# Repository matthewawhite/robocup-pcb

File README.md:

View this project on [CADLAB.io](https://cadlab.io/project/2105). 

RoboCup PCB Repository
===========
Welcome to the Georgia Tech RoboJackets repository for management and storage of RoboCup's hardware files! Additional information about the team and current projects can be found on the [RoboJackets Website](http://www.robojackets.org/teams/robocup/) and the [RoboJacket Wiki](http://wiki.robojackets.org/w/RoboCup).

If you are a new member to the RoboCup electrical team and have never used *[git version control](http://git-scm.com/)* before, we highly recommend that you familiarize yourself with it.

## Prerequisites
- A computer configured with git [[Windows](https://windows.github.com)] [[Mac](https://mac.github.com/)]
- An installation of [EAGLE](http://www.cadsoftusa.com/)

## Using this Repository
Most CAD files found here are [EAGLE](http://www.cadsoftusa.com/) files. However, some older archived files were created using [PCB](http://pcb.geda-project.org) (a program that is part of the [gEDA project](http://www.geda-project.org)). Users will find the following items here:
- Control, Kicker, Antenna, and Base Station files
- Gerber files for most PCB designs
- RoboCup libraries
- DRU rulesets (for checking for errors)
- CAM Jobs (for exporting gerber files)

### Setup libraries in EAGLE

1. Downloading the libraries

	Once your computer is setup with git, the following lines can be used on any operating system within a *[terminal](http://en.wikipedia.org/wiki/Computer_terminal)* configured with git. Users who are using a GUI interface for git should simply add the respective repositories through the interface.

	```shell
    # Download the initial files
	$ git clone https://github.com/robojackets/robocup-pcb

    # Go into our new directory
    cd robocup-pcb

    # Download additional 3rd party libraries
    git submodule update --init
	```
2. Add the new directory locations to EAGLE:

	From EAGLE's Control Panel, navigate to the *Directories* window: *Options -> Directories*.

    Find the *Libraries* text box, and add the directory paths where the repositories were cloned from step 1. Don't forget to also include the path for the *[RoboJackets libraries](https://github.com/RoboJackets/robocup-pcb/tree/master/lib)*!

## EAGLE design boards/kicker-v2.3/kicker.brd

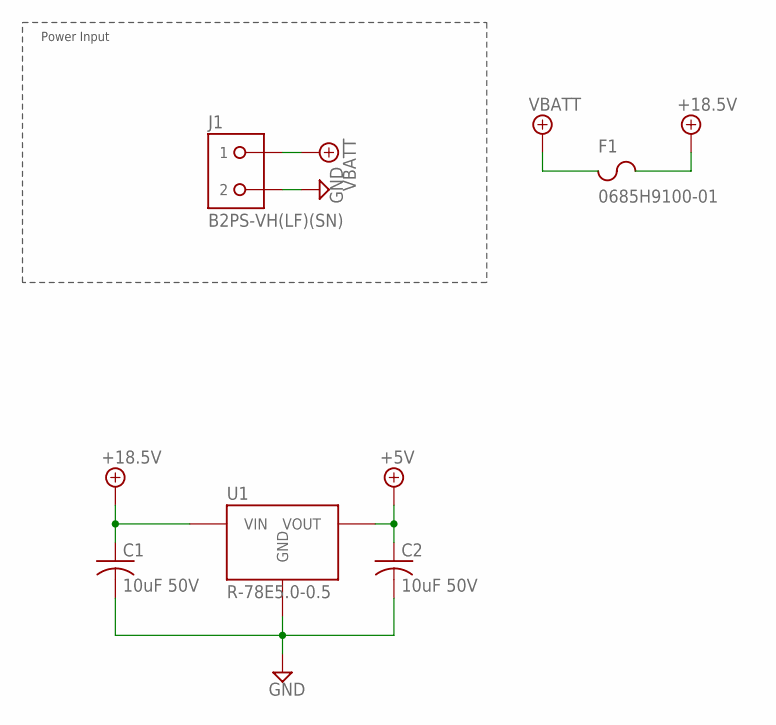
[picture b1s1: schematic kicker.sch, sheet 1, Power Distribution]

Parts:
C1, C2: 10uF 50V; C0603
F1: 0685H9100-01; F1206
J1: B2PS-VH(LF)(SN); B2PS-CENTERED
U1: R-78E5.0-0.5; R-78E

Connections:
+5V: C2.1, U1.3 (VOUT); also elsewhere on the board
+18.5V: C1.1, F1.2, U1.1 (VIN); also elsewhere on the board
GND: C1.2, C2.2, J1.2, U1.2 (GND); also elsewhere on the board
VBATT: F1.1, J1.1

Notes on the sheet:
Power Input

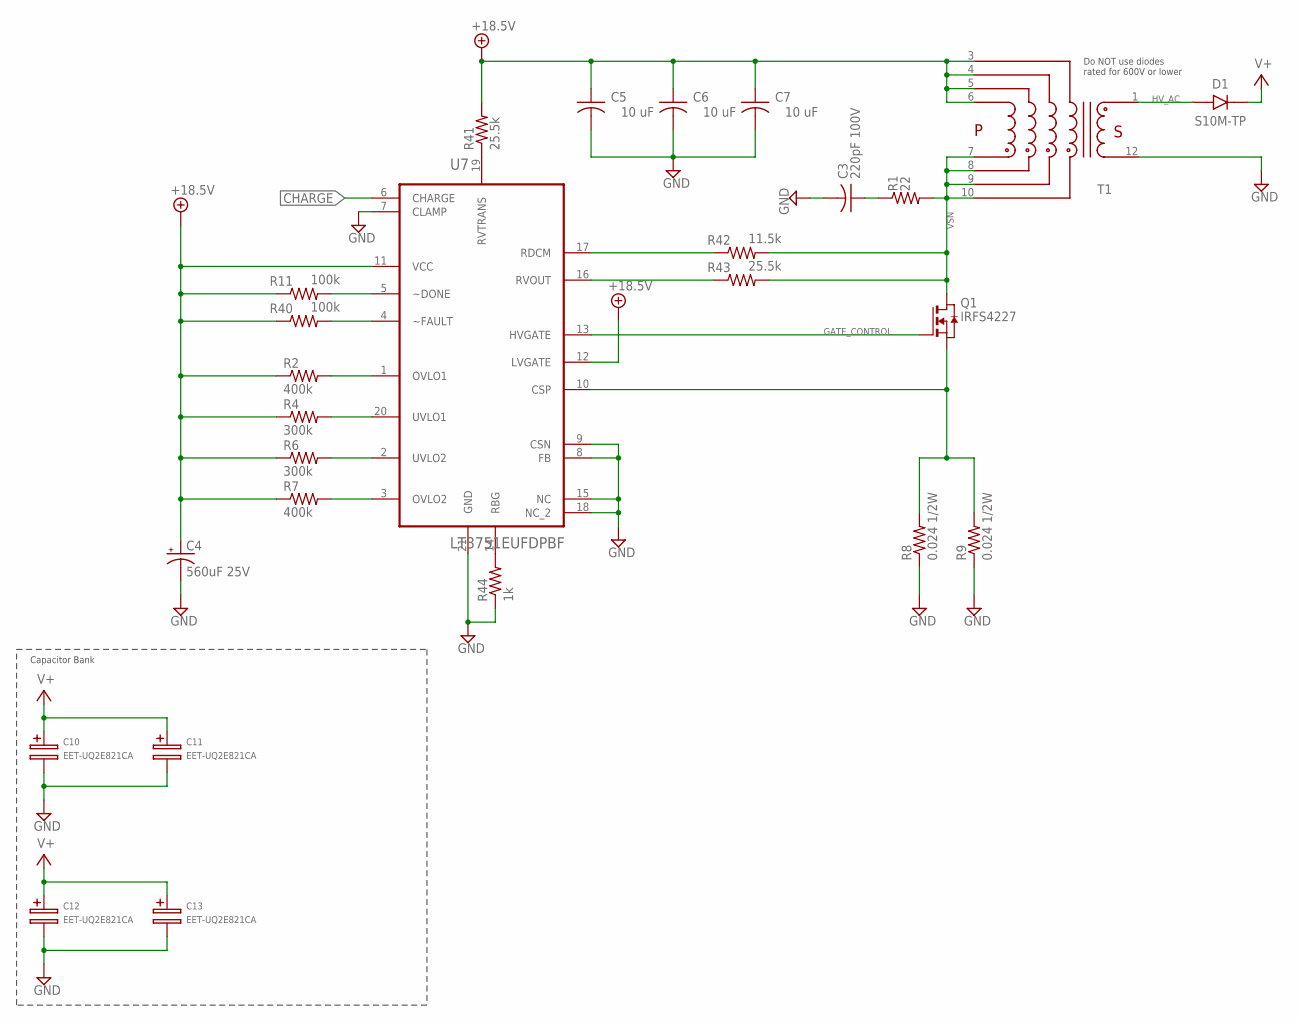
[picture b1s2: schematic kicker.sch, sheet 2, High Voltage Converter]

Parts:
C3: 220pF 100V; C0603
C4: 560uF 25V; UD-10X10_NICHICON
C5, C6, C7: 10 uF; C0603
C10, C11: EET-UQ2E821CA; 25MM-DIA_40MM-HGT_HORIZ
C12, C13: EET-UQ2E821CA; 25MM-DIA_40MM-HGT_HORIZ_MIRRORED
D1: S10M-TP; DO-214AB
Q1: IRFS4227; D2PAK
R1: 22; R0805
R2, R7: 400k; R0603
R4, R6: 300k; R0603
R8, R9: 0.024 1/2W; R1206
R11, R40: 100k; R0603
R41, R43: 25.5k; R0603
R42: 11.5k; R0603
R44: 1k; R0603
T1: DA203X-ALDA2034; DA2034
U7: LT3751EUFDPBF; QFN50P400X500X80-21N

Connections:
+18.5V: C4.+, C5.1, C6.1, C7.1, R2.1, R4.1, R6.1, R7.1, R11.1, R40.1, R41.2, T1.3, T1.4, T1.5, T1.6, U7.11 (VCC), U7.12 (LVGATE); also elsewhere on the board
CHARGE: U7.6 (CHARGE); also elsewhere on the board
GATE_CONTROL: Q1.1 (G), U7.13 (HVGATE)
GND: C3.2, C4.-, C5.2, C6.2, C7.2, C10.-, C11.-, C12.-, C13.-, R8.1, R9.1, R44.1, T1.12, U7.7 (CLAMP), U7.8 (FB), U7.9 (CSN), U7.15 (NC), U7.18 (NC_2), U7.21 (GND); also elsewhere on the board
HV_AC: D1.A, T1.1
unnamed: R7.2, U7.3 (OVLO2)
unnamed: R6.2, U7.2 (UVLO2)
unnamed: R4.2, U7.20 (UVLO1)
unnamed: R2.2, U7.1 (OVLO1)
unnamed: R11.2, U7.5 (~DONE)
unnamed: R40.2, U7.4 (~FAULT)
unnamed: R41.1, U7.19 (RVTRANS)
unnamed: R42.1, U7.17 (RDCM)
unnamed: R43.1, U7.16 (RVOUT)
unnamed: R44.2, U7.14 (RBG)
unnamed: C3.1, R1.1
SENSE: Q1.3 (S), R8.2, R9.2, U7.10 (CSP)
V+: C10.+, C11.+, C12.+, C13.+, D1.C; also elsewhere on the board
VSN: Q1.2 (D), R1.2, R42.2, R43.2, T1.7, T1.8, T1.9, T1.10

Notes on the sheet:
Do NOT use diodes rated for 600V or lower
Capacitor Bank

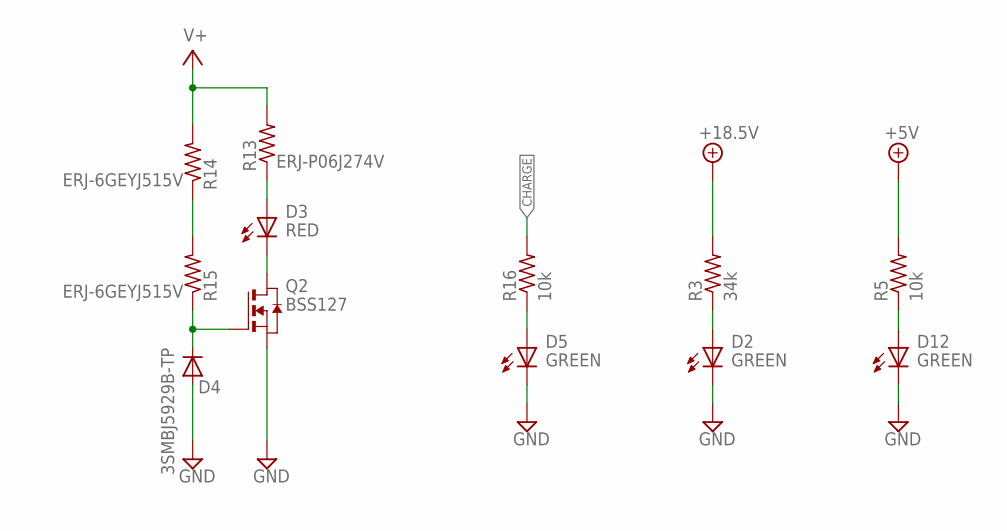
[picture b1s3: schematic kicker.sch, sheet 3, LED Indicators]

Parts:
D2, D5, D12: GREEN; CHIP-LED0603
D3: RED; CHIP-LED0603
D4: 3SMBJ5929B-TP; DO214AA
Q2: BSS127; SOT-23-3
R3: 34k; R0603
R5, R16: 10k; R0603
R13: ERJ-P06J274V; R0805
R14, R15: ERJ-6GEYJ515V; R0805

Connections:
+5V: R5.2; also elsewhere on the board
+18.5V: R3.2; also elsewhere on the board
CHARGE: R16.2; also elsewhere on the board
GND: D2.C (K), D4.A, D5.C (K), D12.C (K), Q2.2 (S); also elsewhere on the board
unnamed: D3.A, R13.1
unnamed: D3.C (K), Q2.3 (D)
unnamed: D5.A, R16.1
unnamed: R14.1, R15.2
unnamed: D4.C, Q2.1 (G), R15.1
unnamed: D2.A, R3.1
unnamed: D12.A, R5.1
V+: R13.2, R14.2; also elsewhere on the board

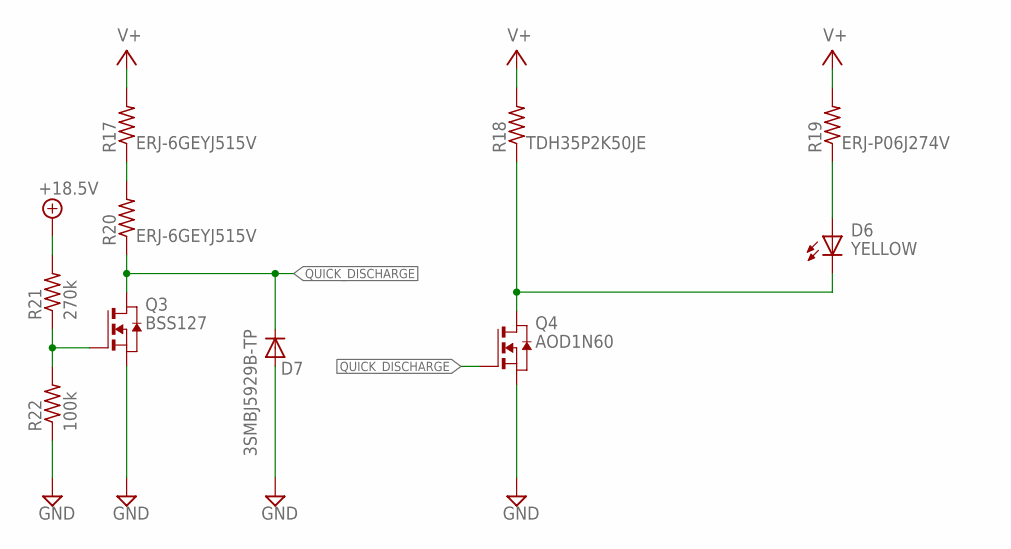
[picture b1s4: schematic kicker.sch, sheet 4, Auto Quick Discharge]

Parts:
D6: YELLOW; CHIP-LED0603
D7: 3SMBJ5929B-TP; DO214AA
Q3: BSS127; SOT-23-3
Q4: AOD1N60; DPAK
R17, R20: ERJ-6GEYJ515V; R0805
R18: TDH35P2K50JE; DPAK_TDH
R19: ERJ-P06J274V; R0805
R21: 270k; R0603
R22: 100k; R0603

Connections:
+18.5V: R21.2; also elsewhere on the board
GND: D7.A, Q3.2 (S), Q4.3 (S), R22.1; also elsewhere on the board
unnamed: R17.1, R20.2
unnamed: Q3.1 (G), R21.1, R22.2
unnamed: D6.C (K), Q4.FIN (D), R18.1 (PIN1)
unnamed: D6.A, R19.1
QUICK_DISCHARGE: D7.C, Q3.3 (D), Q4.1 (G), R20.1
V+: R17.2, R18.2 (PIN2), R19.2; also elsewhere on the board

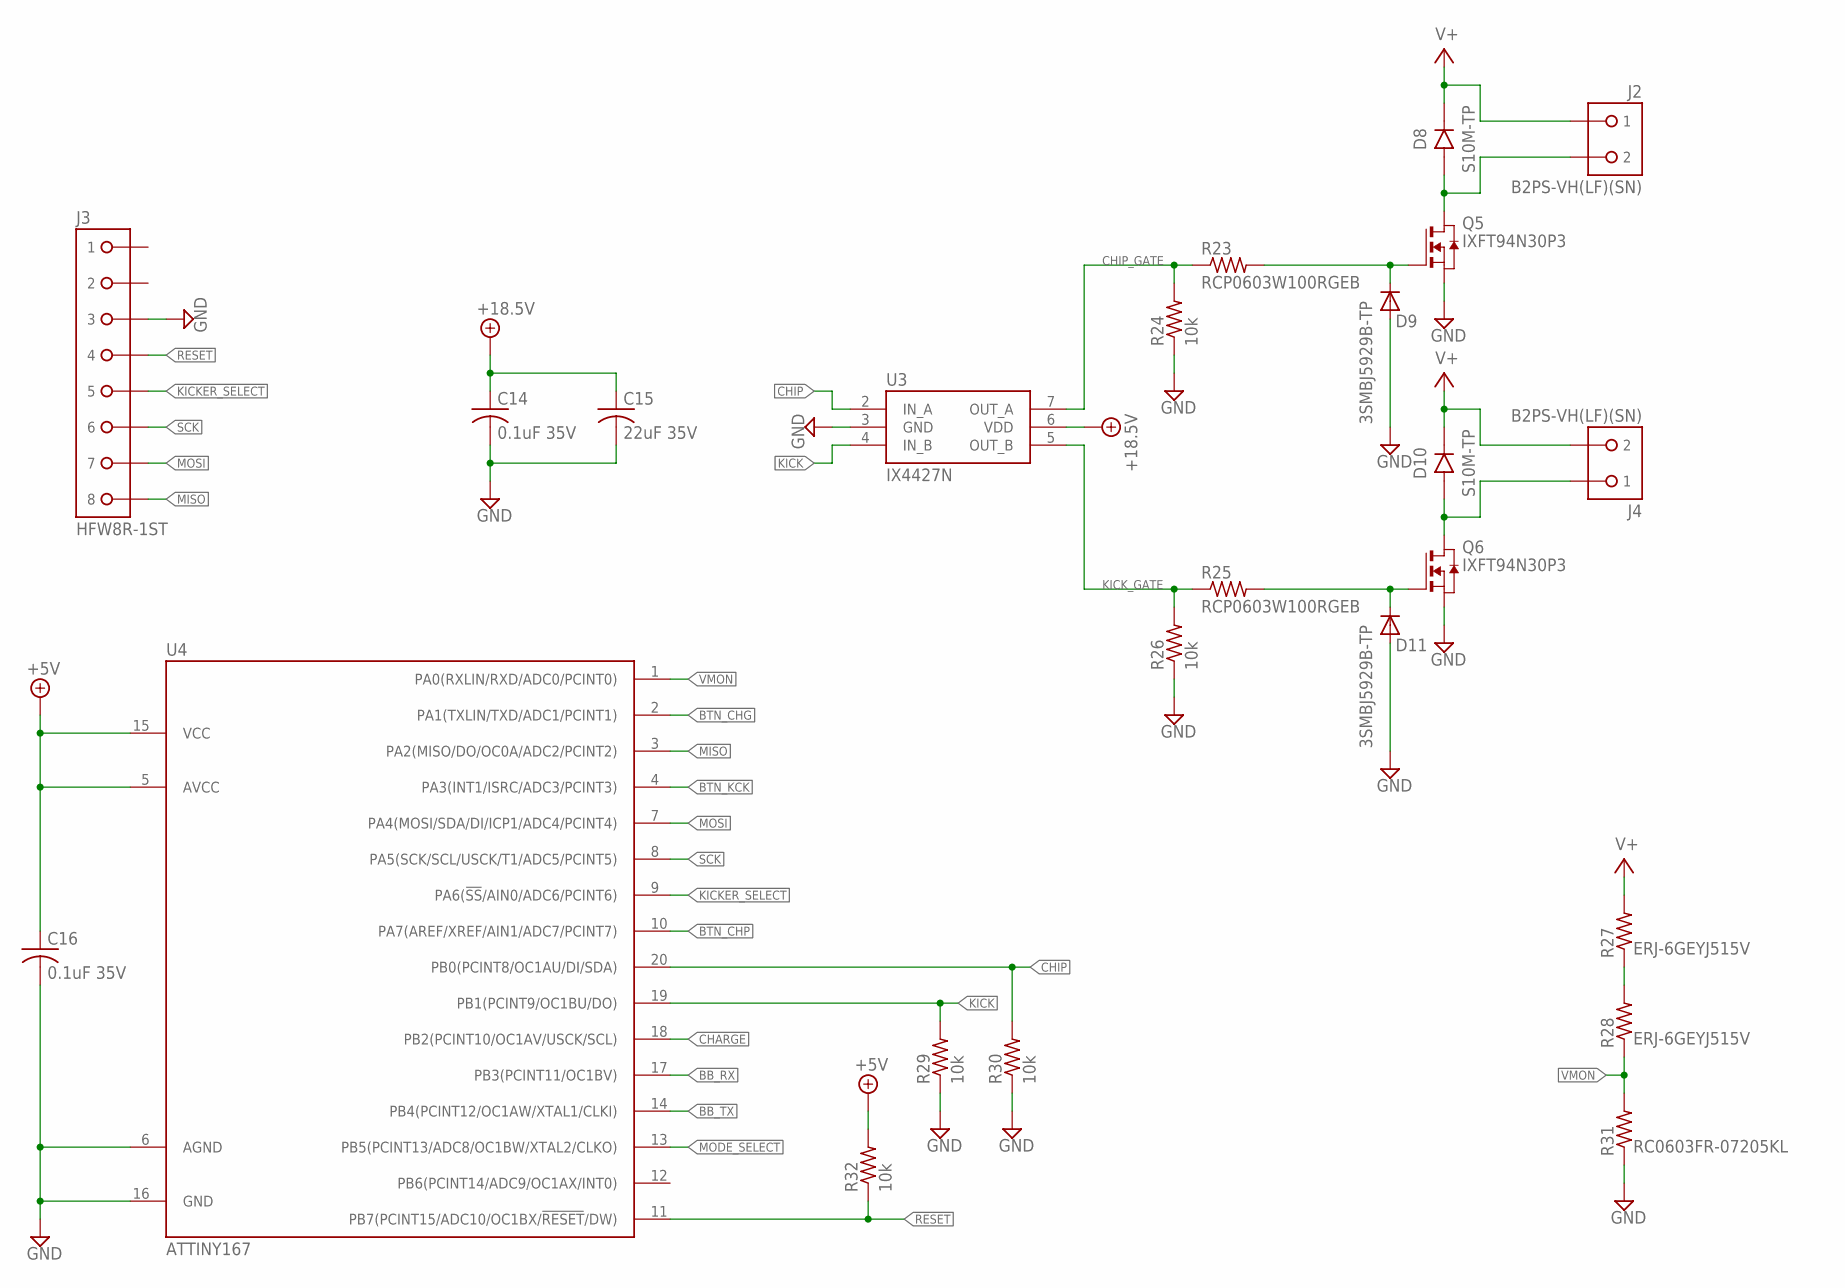
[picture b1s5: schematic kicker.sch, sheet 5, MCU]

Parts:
C14, C16: 0.1uF 35V; C0603
C15: 22uF 35V; C0805
D8, D10: S10M-TP; DO-214AB
D9, D11: 3SMBJ5929B-TP; DO214AA
J2, J4: B2PS-VH(LF)(SN); B2PS-CENTERED
J3: HFW8R-1ST
Q5, Q6: IXFT94N30P3; TO-268
R23, R25: RCP0603W100RGEB; R0603W
R24, R26, R29, R30, R32: 10k; R0603
R27, R28: ERJ-6GEYJ515V; R0805
R31: RC0603FR-07205KL; R0603
U3: IX4427N; SOIC-8
U4: ATTINY167; SOIC-20

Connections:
!BTN_CHG: U4.2 (PA1(TXLIN/TXD/ADC1/PCINT1)); also elsewhere on the board
!BTN_CHP: U4.10 (PA7(AREF/XREF/AIN1/ADC7/PCINT7)); also elsewhere on the board
!BTN_KCK: U4.4 (PA3(INT1/ISRC/ADC3/PCINT3)); also elsewhere on the board
!KICKER_SELECT: J3.5, U4.9 (PA6(!SS!/AIN0/ADC6/PCINT6))
!RESET: J3.4, R32.1, U4.11 (PB7(PCINT15/ADC10/OC1BX/!RESET!/DW))
+5V: C16.1, R32.2, U4.5 (AVCC), U4.15 (VCC); also elsewhere on the board
+18.5V: C14.1, C15.1, U3.6 (VDD); also elsewhere on the board
BB_RX: U4.17 (PB3(PCINT11/OC1BV)); also elsewhere on the board
BB_TX: U4.14 (PB4(PCINT12/OC1AW/XTAL1/CLKI)); also elsewhere on the board
CHARGE: U4.18 (PB2(PCINT10/OC1AV/USCK/SCL)); also elsewhere on the board
CHIP: R30.2, U3.2 (IN_A), U4.20 (PB0(PCINT8/OC1AU/DI/SDA))
CHIPPER: D8.A, J2.2, Q5.4 (D)
CHIP_GATE: R23.1 (PIN1), R24.2, U3.7 (OUT_A)
GND: C14.2, C15.2, C16.2, D9.A, D11.A, J3.3, Q5.3 (S), Q6.3 (S), R24.1, R26.1, R29.1, R30.1, R31.1, U3.3 (GND), U4.6 (AGND), U4.16 (GND); also elsewhere on the board
KICK: R29.2, U3.4 (IN_B), U4.19 (PB1(PCINT9/OC1BU/DO))
KICKER: D10.A, J4.1, Q6.4 (D)
KICK_GATE: R25.1 (PIN1), R26.2, U3.5 (OUT_B)
MISO: J3.8, U4.3 (PA2(MISO/DO/OC0A/ADC2/PCINT2))
MODE_SELECT: U4.13 (PB5(PCINT13/ADC8/OC1BW/XTAL2/CLKO)); also elsewhere on the board
MOSI: J3.7, U4.7 (PA4(MOSI/SDA/DI/ICP1/ADC4/PCINT4))
unnamed: D9.C, Q5.1 (G), R23.2 (PIN2)
unnamed: D11.C, Q6.1 (G), R25.2 (PIN2)
unnamed: R27.1, R28.2
SCK: J3.6, U4.8 (PA5(SCK/SCL/USCK/T1/ADC5/PCINT5))
V+: D8.C, D10.C, J2.1, J4.2, R27.2; also elsewhere on the board
VMON: R28.1, R31.2, U4.1 (PA0(RXLIN/RXD/ADC0/PCINT0))

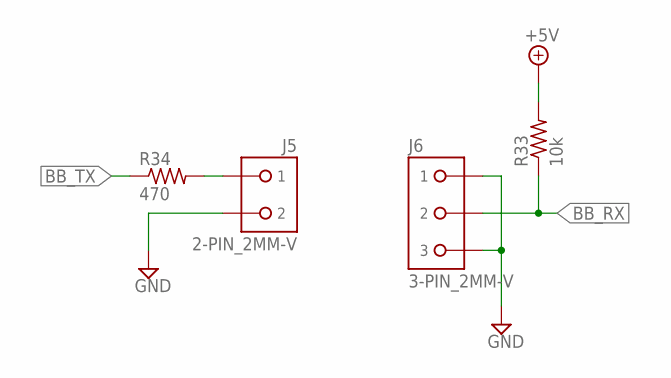
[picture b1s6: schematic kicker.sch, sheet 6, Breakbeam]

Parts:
J5: 2-PIN_2MM-V; 2MM-2-V
J6: 3-PIN_2MM-V; 2MM-3-V
R33: 10k; R0603
R34: 470; R0603

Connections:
+5V: R33.2; also elsewhere on the board
BB_RX: J6.2, R33.1; also elsewhere on the board
BB_TX: R34.1; also elsewhere on the board
GND: J5.2, J6.1, J6.3; also elsewhere on the board
unnamed: J5.1, R34.2

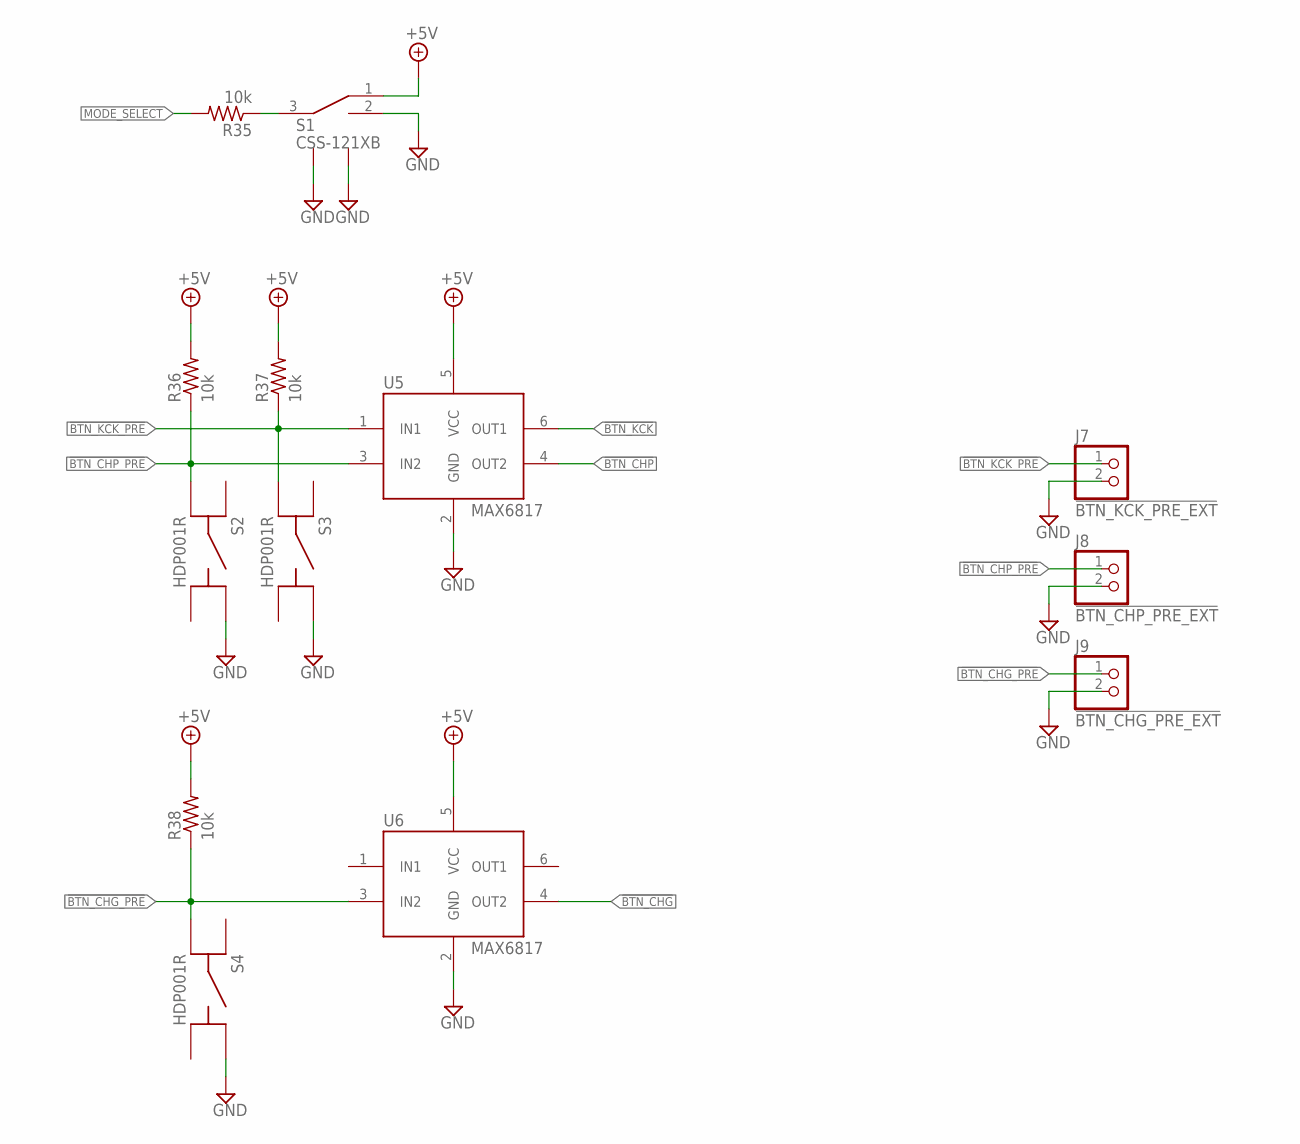
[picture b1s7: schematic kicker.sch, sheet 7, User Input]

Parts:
J7: !BTN_KCK_PRE_EXT; 1X2
J8: !BTN_CHP_PRE_EXT; 1X2
J9: !BTN_CHG_PRE_EXT; 1X2
R35, R36, R37, R38: 10k; R0603
S1: CSS-121XB
S2, S3, S4: HDP001R
U5, U6: MAX6817; SOT-23-6

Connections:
!BTN_CHG: U6.4 (OUT2); also elsewhere on the board
!BTN_CHG_PRE: J9.1, R38.1, S4.C (A2), U6.3 (IN2)
!BTN_CHP: U5.4 (OUT2); also elsewhere on the board
!BTN_CHP_PRE: J8.1, R36.1, S2.C (A2), U5.3 (IN2)
!BTN_KCK: U5.6 (OUT1); also elsewhere on the board
!BTN_KCK_PRE: J7.1, R37.1, S3.C (A2), U5.1 (IN1)
+5V: R36.2, R37.2, R38.2, S1.1 (A), U5.5 (VCC), U6.5 (VCC); also elsewhere on the board
GND: J7.2, J8.2, J9.2, S1.2 (B), S1.LEG1, S1.LEG4 (LEG2), S2.B (B1), S3.B (B1), S4.B (B1), U5.2 (GND), U6.2 (GND); also elsewhere on the board
MODE_SELECT: R35.2; also elsewhere on the board
unnamed: R35.1, S1.3 (COMMON)

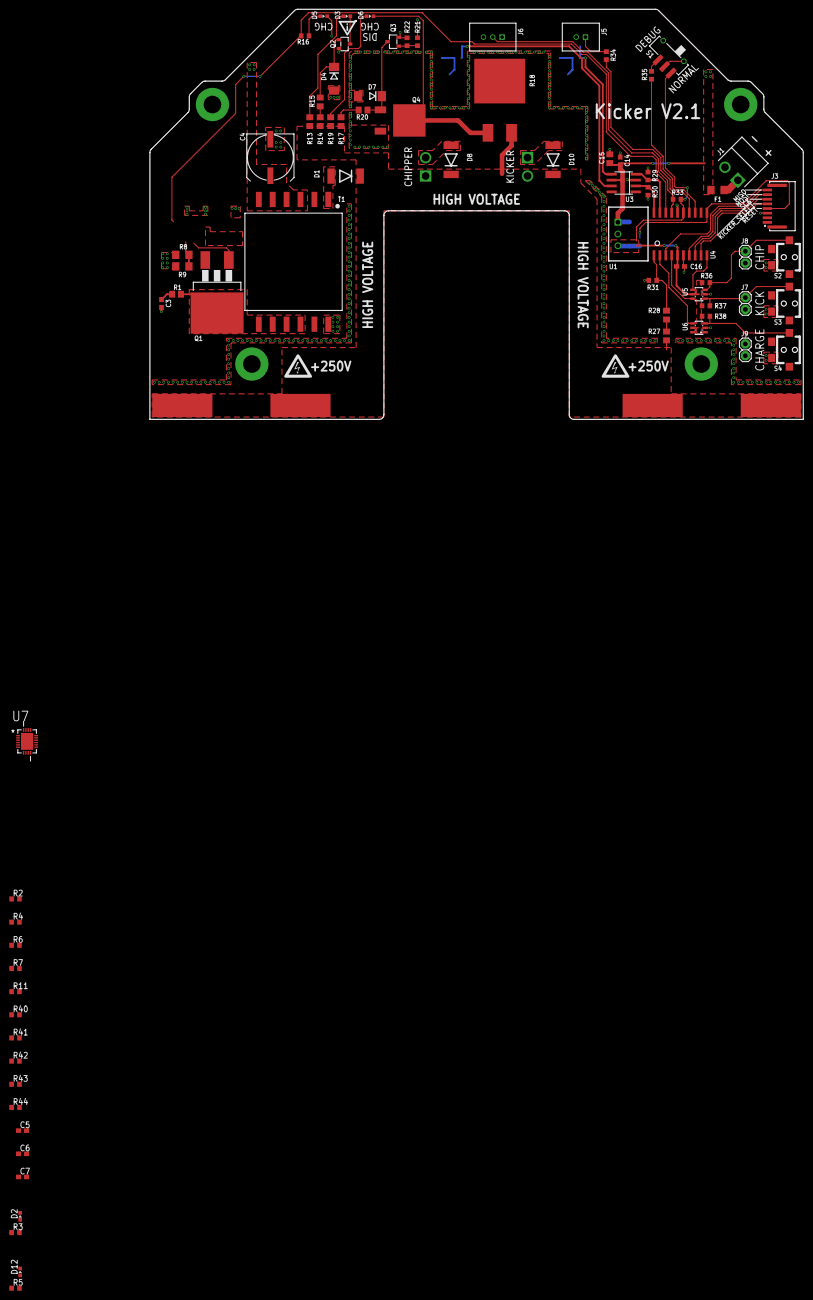
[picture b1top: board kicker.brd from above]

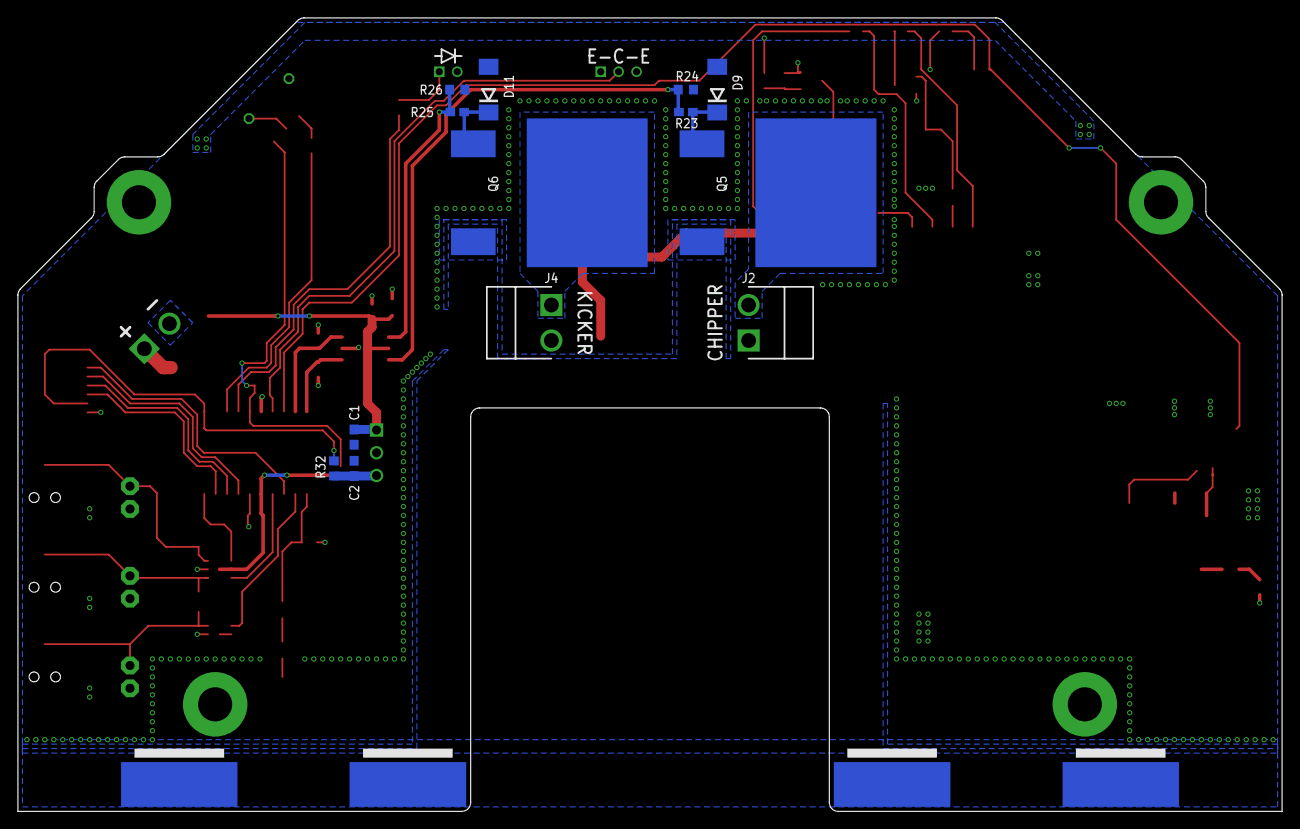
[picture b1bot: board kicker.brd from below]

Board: 2 copper layers, 141.0 x 88.5 mm, 97 parts (13 on the bottom side), 59 nets.

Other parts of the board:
U$1, U$2: HV_WARNING
U$4: WARNING2

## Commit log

2016-05-18 nuked repo contents
2016-05-18 updated pcb gallery
2018-04-21 Kicker board revision 2.3: Replaced flyback controller with LT3751; added LED indicators for +18.5V and +5V
2018-04-21 Remove old versions of kicker board
2019-09-11 Backlink to CADLAB.io has been added.
2019-09-11 Removed old versions to make cadlab run faster
